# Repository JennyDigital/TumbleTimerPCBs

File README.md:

# TumbleTimer PCBs

The TumbleTimer code needs a place to live.  Whilst software is intangible, hardware is the bit that hurts your toe if you kick it.  The two go together like ham and eggs.

I made these PCBs to make my tumble dryer work again and got just a little carried away.

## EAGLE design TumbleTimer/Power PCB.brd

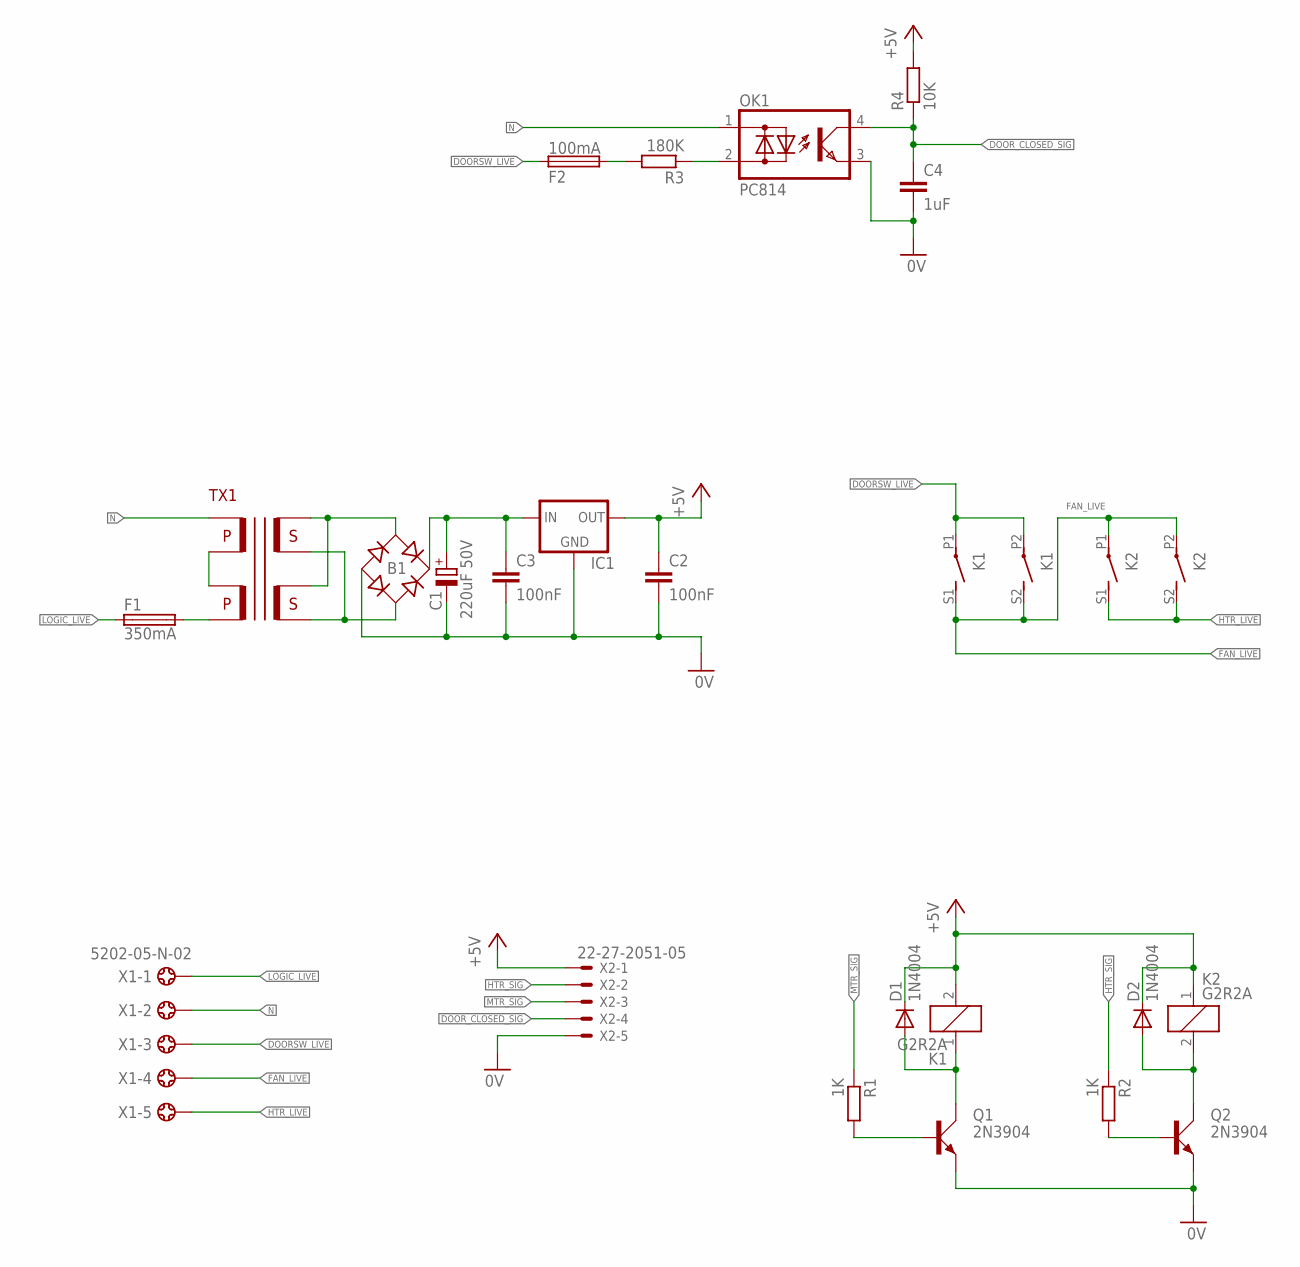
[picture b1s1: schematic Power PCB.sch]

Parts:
B1: RECTIFIER-RB1A; RB1A
C1: 220uF 50V; E3,5-8
C2, C3: 100nF; C025-025X050
C4: 1uF; C025-025X050
D1, D2: 1N4004; DO41-10
F1: 350mA; SH25
F2: 100mA; SH25
IC1: V_REG_78XX-TO-220; TO-220-ALT
K1, K2: G2R2A
OK1: PC814; DIL04
Q1, Q2: 2N3904; TO92D
R1, R2: 1K; 0207/10
R3: 180K; P0613V
R4: 10K; 0207/10
TX1: RS504-397
X1: 5202-05-N-02
X2: 22-27-2051-05; 6410-05

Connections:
0V: B1.-, C1.-, C2.2, C3.2, C4.2, IC1.GND, OK1.3 (E), Q1.E, Q2.E, X2.5
+5V: C2.1, D1.C, D2.C, IC1.OUT, K1.2, K2.1, R4.2, X2.1
DOORSW_LIVE: F2.1, K1.P1, K1.P2, X1.3
DOOR_CLOSED_SIG: C4.1, OK1.4 (C), R4.1, X2.4
FAN_LIVE: K1.S1 (S), K1.S2 (S), K2.P1, K2.P2, X1.4
HTR_LIVE: K2.S1 (S), K2.S2 (S), X1.5
HTR_SIG: R2.1, X2.2
LOGIC_LIVE: F1.1, X1.1
MTR_SIG: R1.1, X2.3
N: OK1.1 (AC1), TX1.115V1, X1.2
unnamed: OK1.2 (AC2), R3.1
unnamed: F2.2, R3.2
unnamed: F1.2, TX1.0V2
unnamed: TX1.0V1, TX1.115V2
unnamed: B1.AC2, TX1.12V1_0, TX1.12V2_0
unnamed: B1.AC1, TX1.12V1, TX1.12V2
unnamed: B1.+, C1.+, C3.1, IC1.IN
unnamed: D2.A, K2.2, Q2.C
unnamed: D1.A, K1.1, Q1.C
unnamed: Q1.B, R1.2
unnamed: Q2.B, R2.2

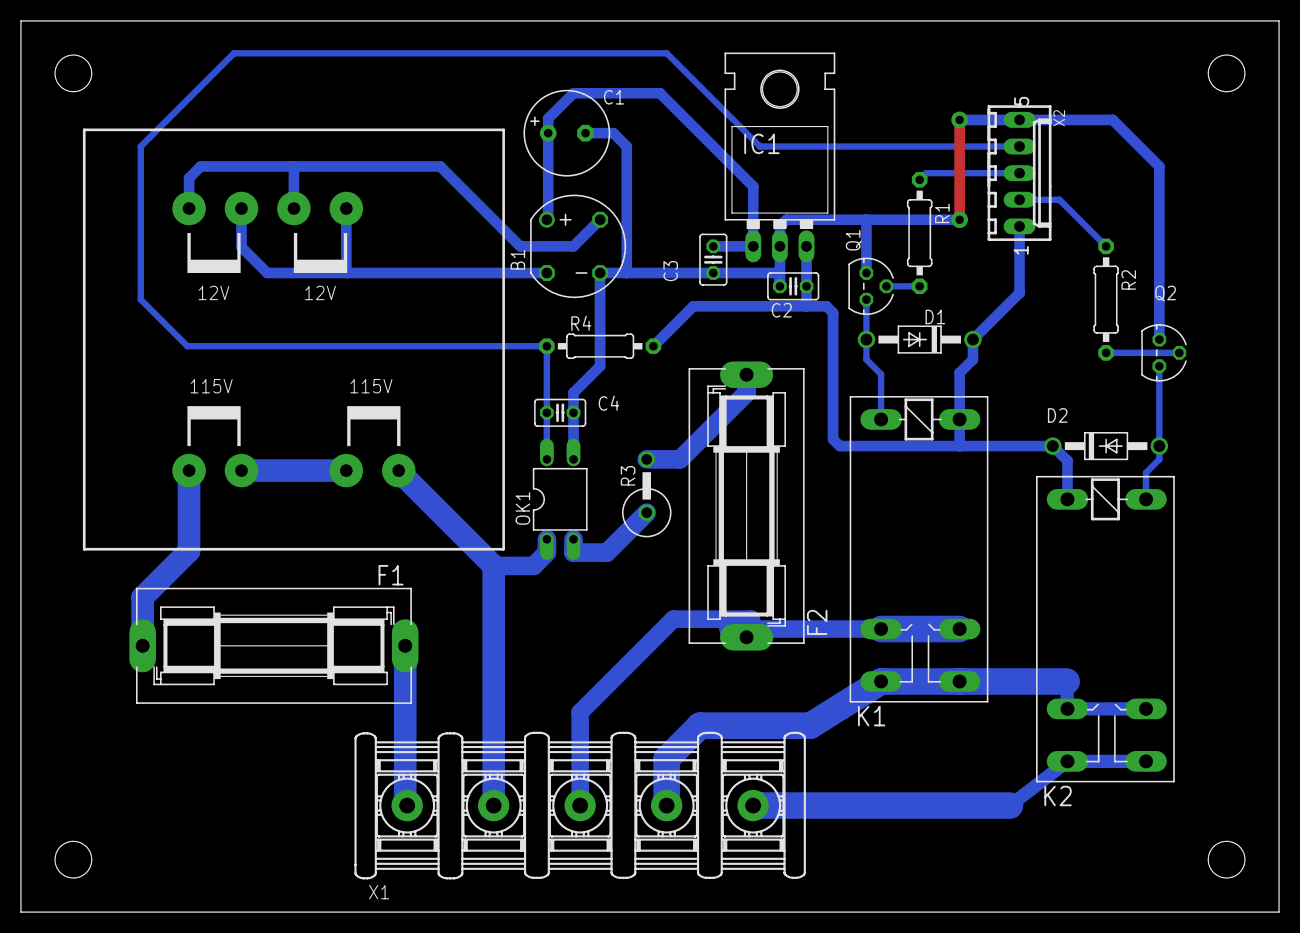
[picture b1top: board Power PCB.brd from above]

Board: 2 copper layers, 120.0 x 85.0 mm, 22 parts (0 on the bottom side), 21 nets.

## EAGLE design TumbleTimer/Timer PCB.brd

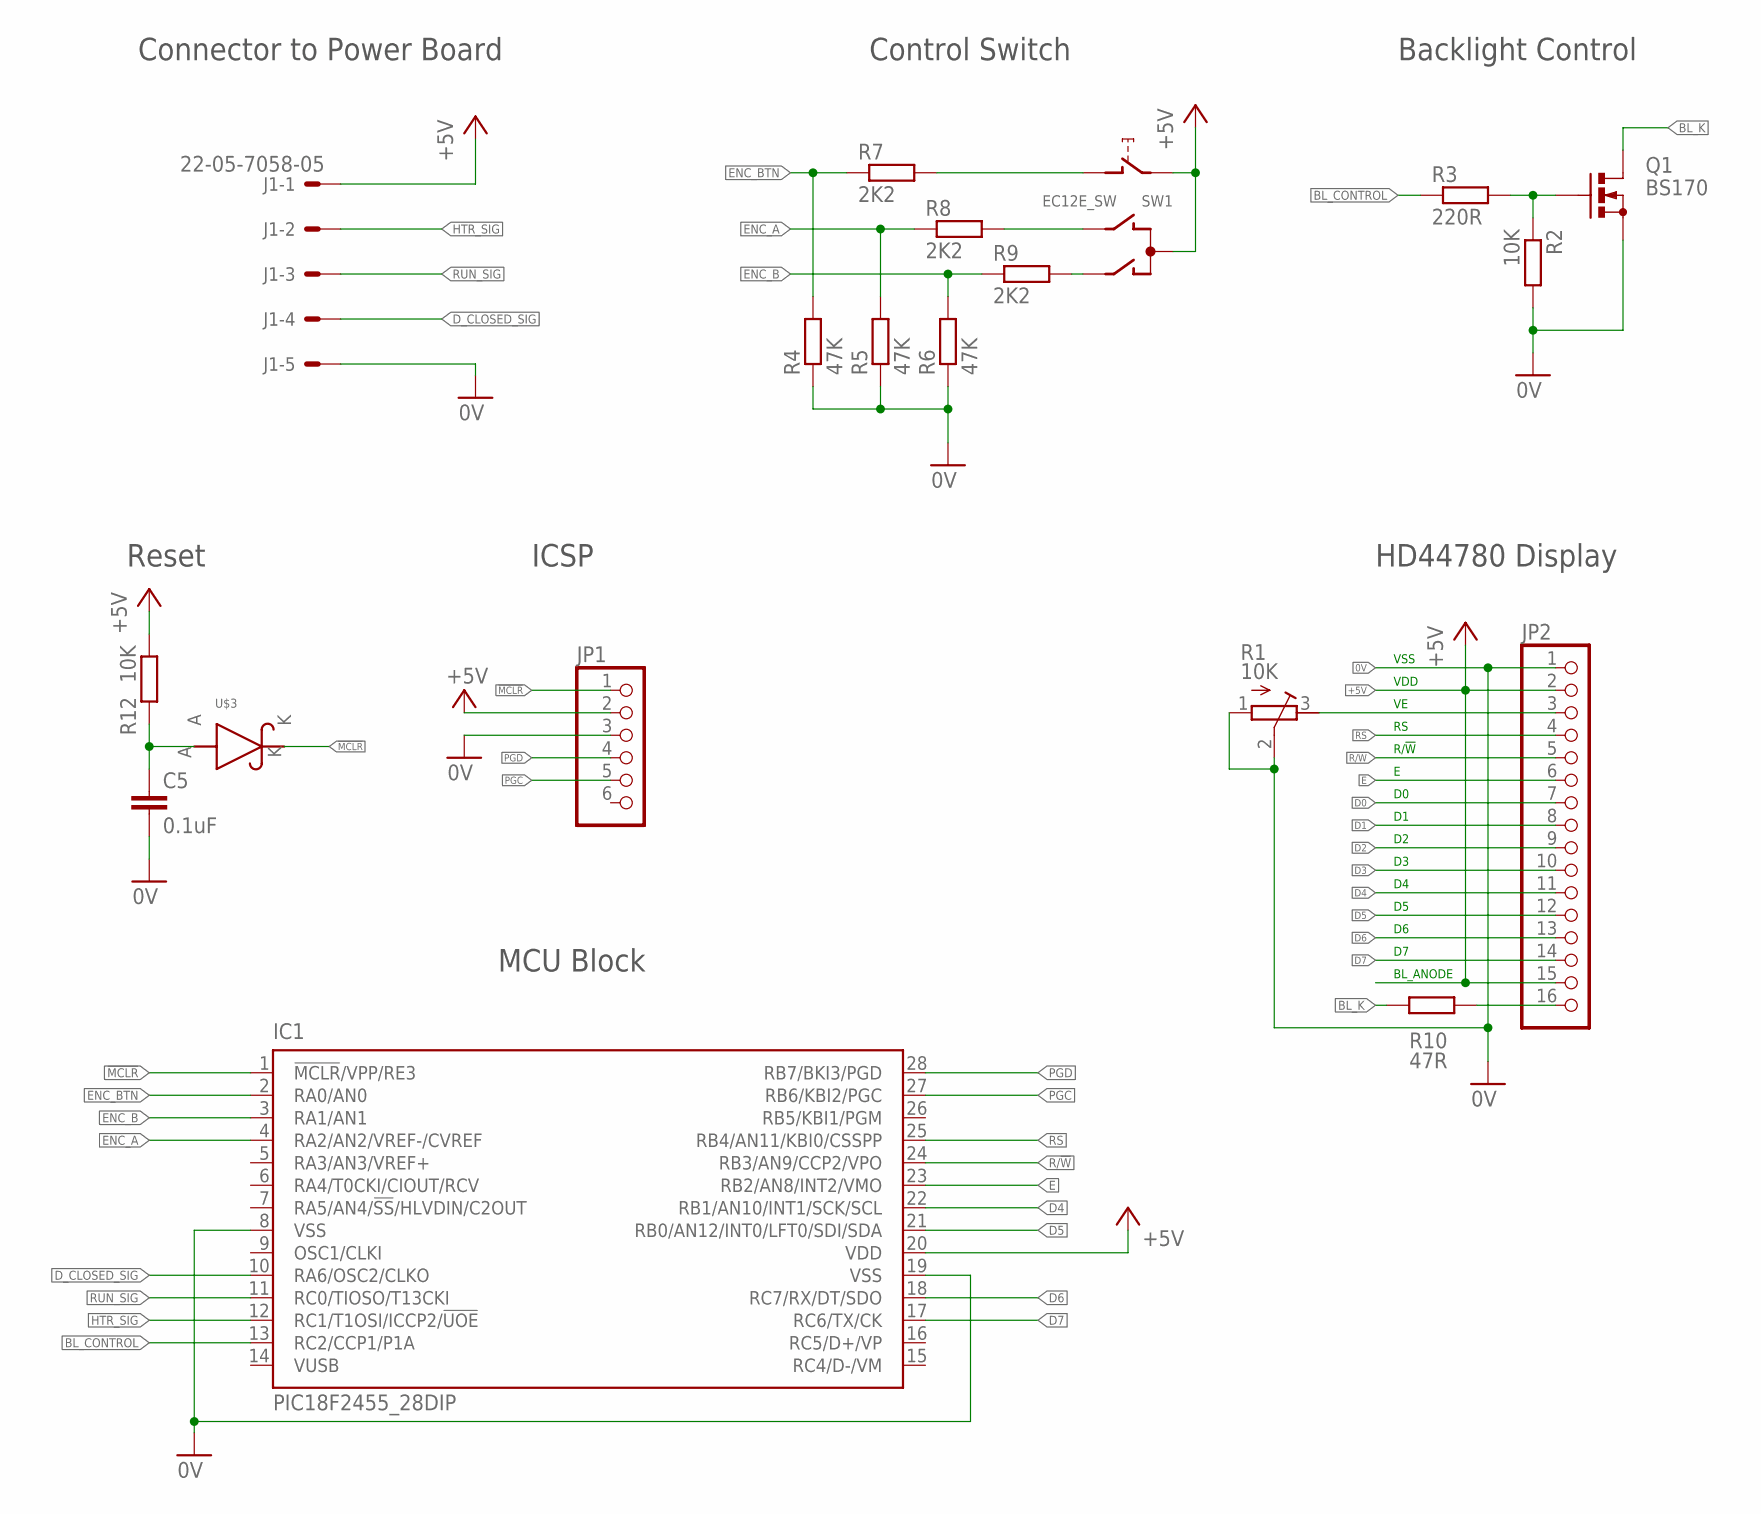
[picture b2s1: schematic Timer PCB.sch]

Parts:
C5: 0.1uF; C0603
IC1: PIC18F2455_28DIP; DIL28-3
J1: 22-05-7058-05; 7395-05
JP1: PINHD-1X6/90; 1X06/90
JP2: PINHD-1X16; 1X16
Q1: BS170; SOT54E
R1: 10K; RTRIM64W
R2: 10K; R0805
R3: 220R; R0805
R4, R5, R6: 47K; R0805
R7, R8, R9: 2K2; R0805
R10: 47R; 0309/12
R12: 10K; R0603
SW1: EC12E_SW; ALPS_EC12E_SW
U$3: ZHCS750; SOT23

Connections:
0V: C5.2, IC1.8 (VSS), IC1.19 (VSS), J1.5, JP1.3, JP2.1, Q1.S, R1.1 (E), R1.2 (S), R2.2, R4.1, R5.1, R6.1
!MCLR: IC1.1 (!MCLR!/VPP/RE3), JP1.1, U$3.K
+5V: IC1.20 (VDD), J1.1, JP1.2, JP2.2, JP2.15, R12.2, SW1.C, SW1.E (2)
BL_CONTROL: IC1.13 (RC2/CCP1/P1A), R3.1
BL_K: Q1.D, R10.1
D0: JP2.7
D1: JP2.8
D2: JP2.9
D3: JP2.10
D4: IC1.22 (RB1/AN10/INT1/SCK/SCL), JP2.11
D5: IC1.21 (RB0/AN12/INT0/LFT0/SDI/SDA), JP2.12
D6: IC1.18 (RC7/RX/DT/SDO), JP2.13
D7: IC1.17 (RC6/TX/CK), JP2.14
D_CLOSED_SIG: IC1.10 (RA6/OSC2/CLKO), J1.4
E: IC1.23 (RB2/AN8/INT2/VMO), JP2.6
ENC_A: IC1.4 (RA2/AN2/VREF-/CVREF), R5.2, R8.1
ENC_B: IC1.3 (RA1/AN1), R6.2, R9.1
ENC_BTN: IC1.2 (RA0/AN0), R4.2, R7.1
HTR_SIG: IC1.12 (RC1/T1OSI/ICCP2/!UOE), J1.2
unnamed: Q1.G, R2.1, R3.2
unnamed: JP2.3, R1.3 (A)
unnamed: R8.2, SW1.B
unnamed: R7.2, SW1.D (1)
unnamed: R9.2, SW1.A
unnamed: JP2.16, R10.2
unnamed: C5.1, R12.1, U$3.A
PGC: IC1.27 (RB6/KBI2/PGC), JP1.5
PGD: IC1.28 (RB7/BKI3/PGD), JP1.4
R/!W: IC1.24 (RB3/AN9/CCP2/VPO), JP2.5
RS: IC1.25 (RB4/AN11/KBI0/CSSPP), JP2.4
RUN_SIG: IC1.11 (RC0/TIOSO/T13CKI), J1.3

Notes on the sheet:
Control Switch
Connector to Power Board
Reset
ICSP
HD44780 Display
VSS
VDD
R/!W
BL_ANODE
Backlight Control
MCU Block

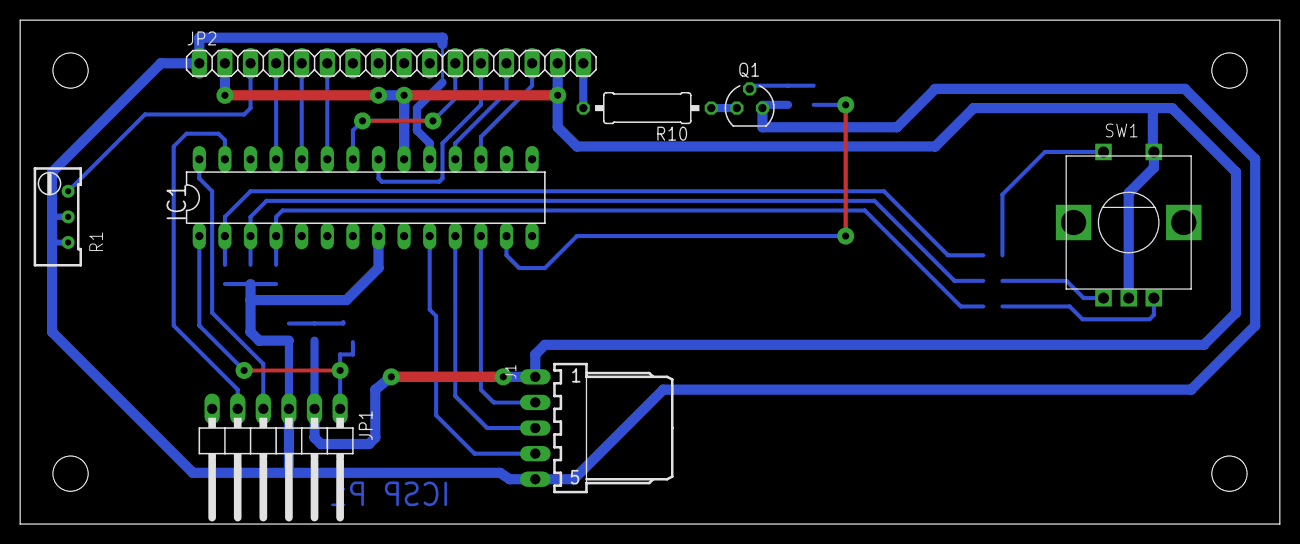
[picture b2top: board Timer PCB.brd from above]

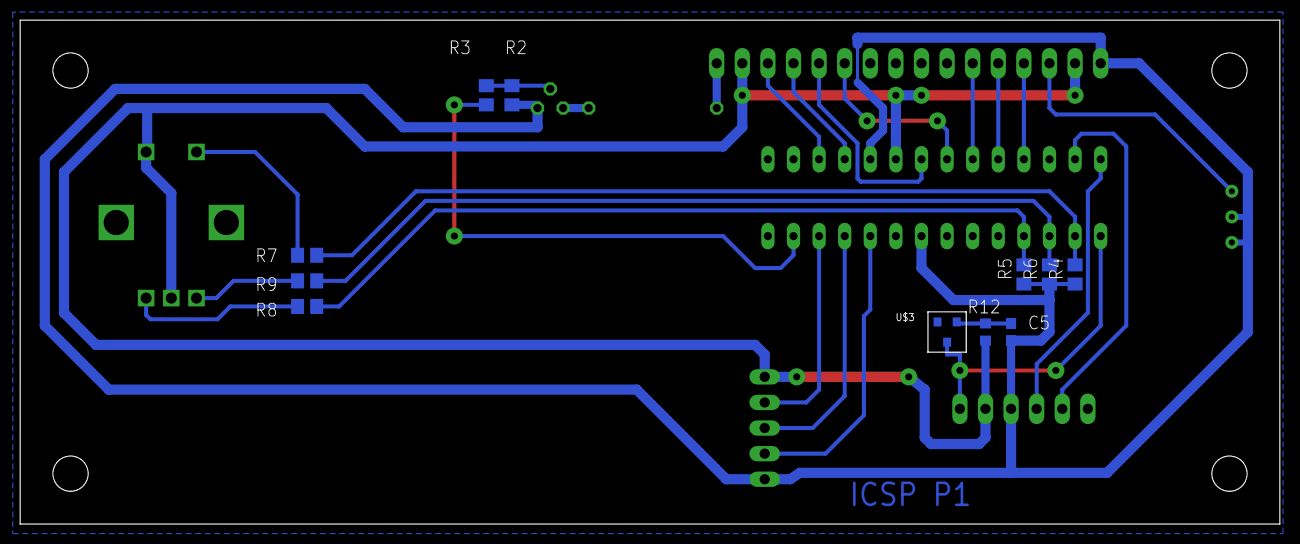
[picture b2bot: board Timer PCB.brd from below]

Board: 2 copper layers, 125.0 x 50.0 mm, 19 parts (11 on the bottom side), 27 nets.

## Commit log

2024-04-21 Added all project files and current gerbers.

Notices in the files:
parts and their libraries:
SparkFun: Licensing: CC v3.0 Share-Alike You are welcome to use this library for commercial purposes.
